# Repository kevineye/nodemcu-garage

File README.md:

# NodeMCU Garage Door Controller

MQTT garage door controller. Also includes temperature and light level logger.

Overall NodeMCU docs:

 * https://nodemcu.readthedocs.io/en/dev/

## Lua firmware setup

#### Build firmware

The lua-based NodeMCU firmware must be built and flashed to the ESP8266. Then the code is uploaded to the firmware's filesystem.

### Build NodeMCU firmware

Build the firmware using the [NodeMCU cloud build service](https://nodemcu-build.com/). Select at least the following modules:

  * CJSON
  * file (default)
  * GPIO (default)
  * MQTT
  * net (default)
  * node (default)
  * timer (default)
  * UART (default)
  * WiFi (default)

Download the "float" version of the build.

### Upload firmware (serial)

Download [esptool,py](https://github.com/themadinventor/esptool) to flash firmware.

    export NODEMCU_DEV=/dev/tty.usbserial*
    alias esptool='esptool.py --port $NODEMCU_DEV --baud 115200'
    
    # upgrade esp SDK
    esptool erase_flash
    esptool write_flash -fm dio -fs 32m 0x00000 nodemcu-master-....bin 0x3fc000 esp_init_data_default.bin
    
    # or just flash
    esptool write_flash -fm dio -fs 32m 0x00000 nodemcu-master-....bin

Programming some modules requires a jumper or button to be set while the device is powered on to enter reprogramming mode.

### Terminal monitor/REPL (serial)

    miniterm.py $NODEMCU_DEV 115200

### Local upload all files (serial)

Download [nodemcu-uploader.py](https://github.com/kmpm/nodemcu-uploader) for local (USB/serial) management.

    export NODEMCU_DEV=/dev/tty.usbserial*
    alias nodemcu-uploader='nodemcu-uploader --port $NODEMCU_DEV'

    nodemcu-uploader upload --restart *.lua *.json && \
    nodemcu-uploader terminal

### Remote management (wifi)

Download [loatool.py](https://github.com/4refr0nt/luatool) for remote (telnet) management.

    export NODEMCU_HOST=<device-ip>
    export NODEMCU_PORT=2323
    alias luatool='luatool --ip $NODEMCU_HOST:$NODEMCU_PORT'

    luatool --restart --src <file.lua>
  
    telnet $NODEMCU_HOST $NODEMCU_PORT
    nc $NODEMCU_HOST $NODEMCU_PORT

These commands only work if a telnet server is running on the device. If the device is otherwise inaccessible, be very
careful not to upload code (such as a broken init.lua) that will fail to connect to wifi, have an error before running 
the telnet server or reboot without allowing time to send some commands.

## Operation

The device will connect to WiFi and MQTT with the settings in config.json. Make sure these are correct before transferring to the device.

### Feedback

When powered on, the LED will give three quick flashes every three seconds until it is successfully connected to WiFi and MQTT. The LED will give two slower flashes when the garage door is opened or closed.

### MQTT

The device will subscribe and publish with a configurable root path, called "home/garage" below, for basic status and configuration.

| Topic                     | Pub/Sub   | Payload   | Description |
|---------------------------|-----------|-----------|-------------|
| `home/garage/ping`        | subscribe | *any*     | Triggers publishing status message. |
| `home/garage/status`      | publish   | *JSON*    | Status info is published at connect and retained. Contains IP address and other info. Marked offline when device is not connected. Retained. |
| `home/garage/config`      | subscribe | key=value | Persistently sets a configuration value in config.json. |
| `home/garage/config`      | subscribe | ping      | Triggers publishing config JSON dump. |
| `home/garage/config`      | subscribe | restart   | Restarts the device. |
| `home/garage/config/json` | publish   | *JSON*    | Configuration values (initially from config.json) are dumped in response to config ping. |
| `home/garage/door/toggle` | subscribe | *any*     | Push the door opener button, i.e. start up or down, or stop if already moving. |
| `home/garage/door`        | publish   | *JSON*    | State of door in json, i.e. {"state":"closed"} or {"state":"open"} |
| `home/garage/sensors`     | publish   | *JSON*    | Sensor data, like {"temperature":72.5,"humidity":65,"light":99}, published every minute. |

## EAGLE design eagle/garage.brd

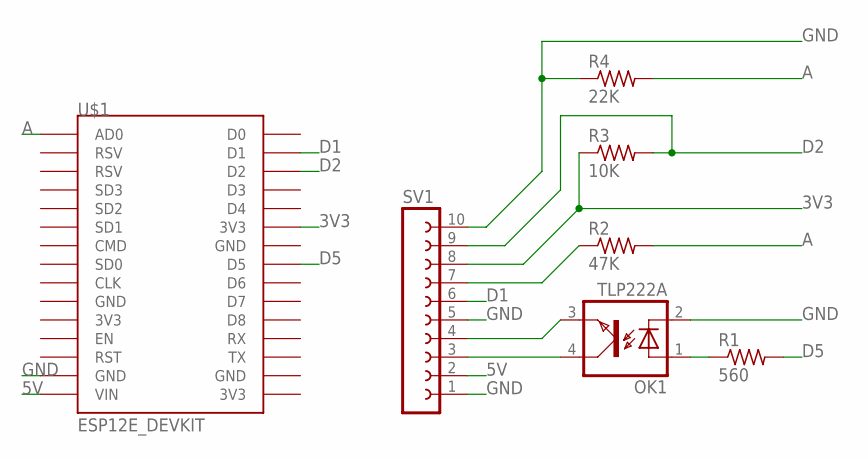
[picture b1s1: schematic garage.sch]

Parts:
OK1: TLP222A; DIL04
R1: 560; 0207/7
R2: 47K; 0207/7
R3: 10K; 0207/7
R4: 22K; 0207/7
SV1: FE10W
U$1: ESP12E_DEVKIT

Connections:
3V3: R3.1, SV1.8, U$1.3V3@1 (3V3)
5V: SV1.2, U$1.VIN
A: R2.2, R4.2, U$1.AD0
D1: SV1.6, U$1.D1
D2: R3.2, SV1.9, U$1.D2
D5: R1.2, U$1.D5
GND: OK1.2 (C), R4.1, SV1.1, SV1.5, SV1.10, U$1.GND@1 (GND)
unnamed: OK1.4 (COL), SV1.3
unnamed: OK1.3 (EMIT), SV1.4
unnamed: OK1.1 (A), R1.1
unnamed: R2.1, SV1.7

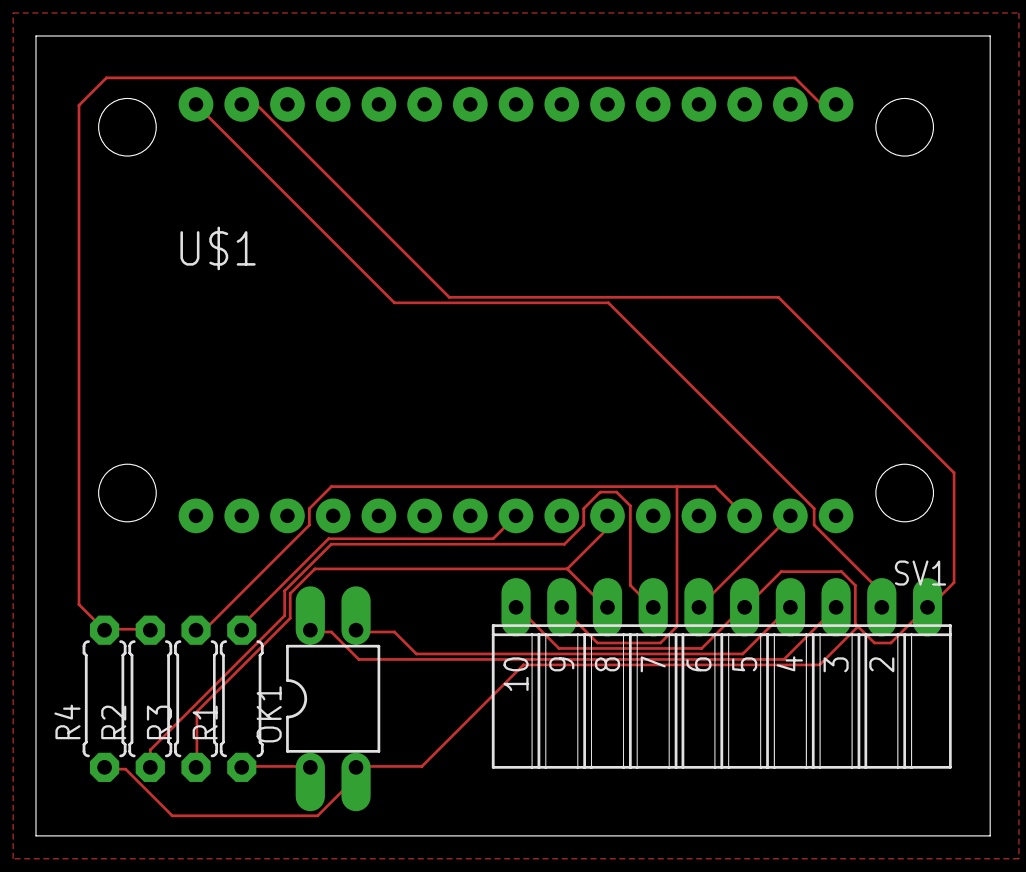
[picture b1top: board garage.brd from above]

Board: 2 copper layers, 53.0 x 44.4 mm, 7 parts (0 on the bottom side), 11 nets.

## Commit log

2016-12-12 moved sensor readings to its own file
2016-12-13 added mock sensors
2016-12-13 added rolling average algorithm to sensor data; added zone reporting
2017-01-14 fixed frequent overflow of reported minutes online
2017-01-16 better tweaking of debounce
2017-10-07 updated for latest nodemcu version
2017-10-07 added open/close command support; tightened heap requirements
2017-10-08 added eagle files
